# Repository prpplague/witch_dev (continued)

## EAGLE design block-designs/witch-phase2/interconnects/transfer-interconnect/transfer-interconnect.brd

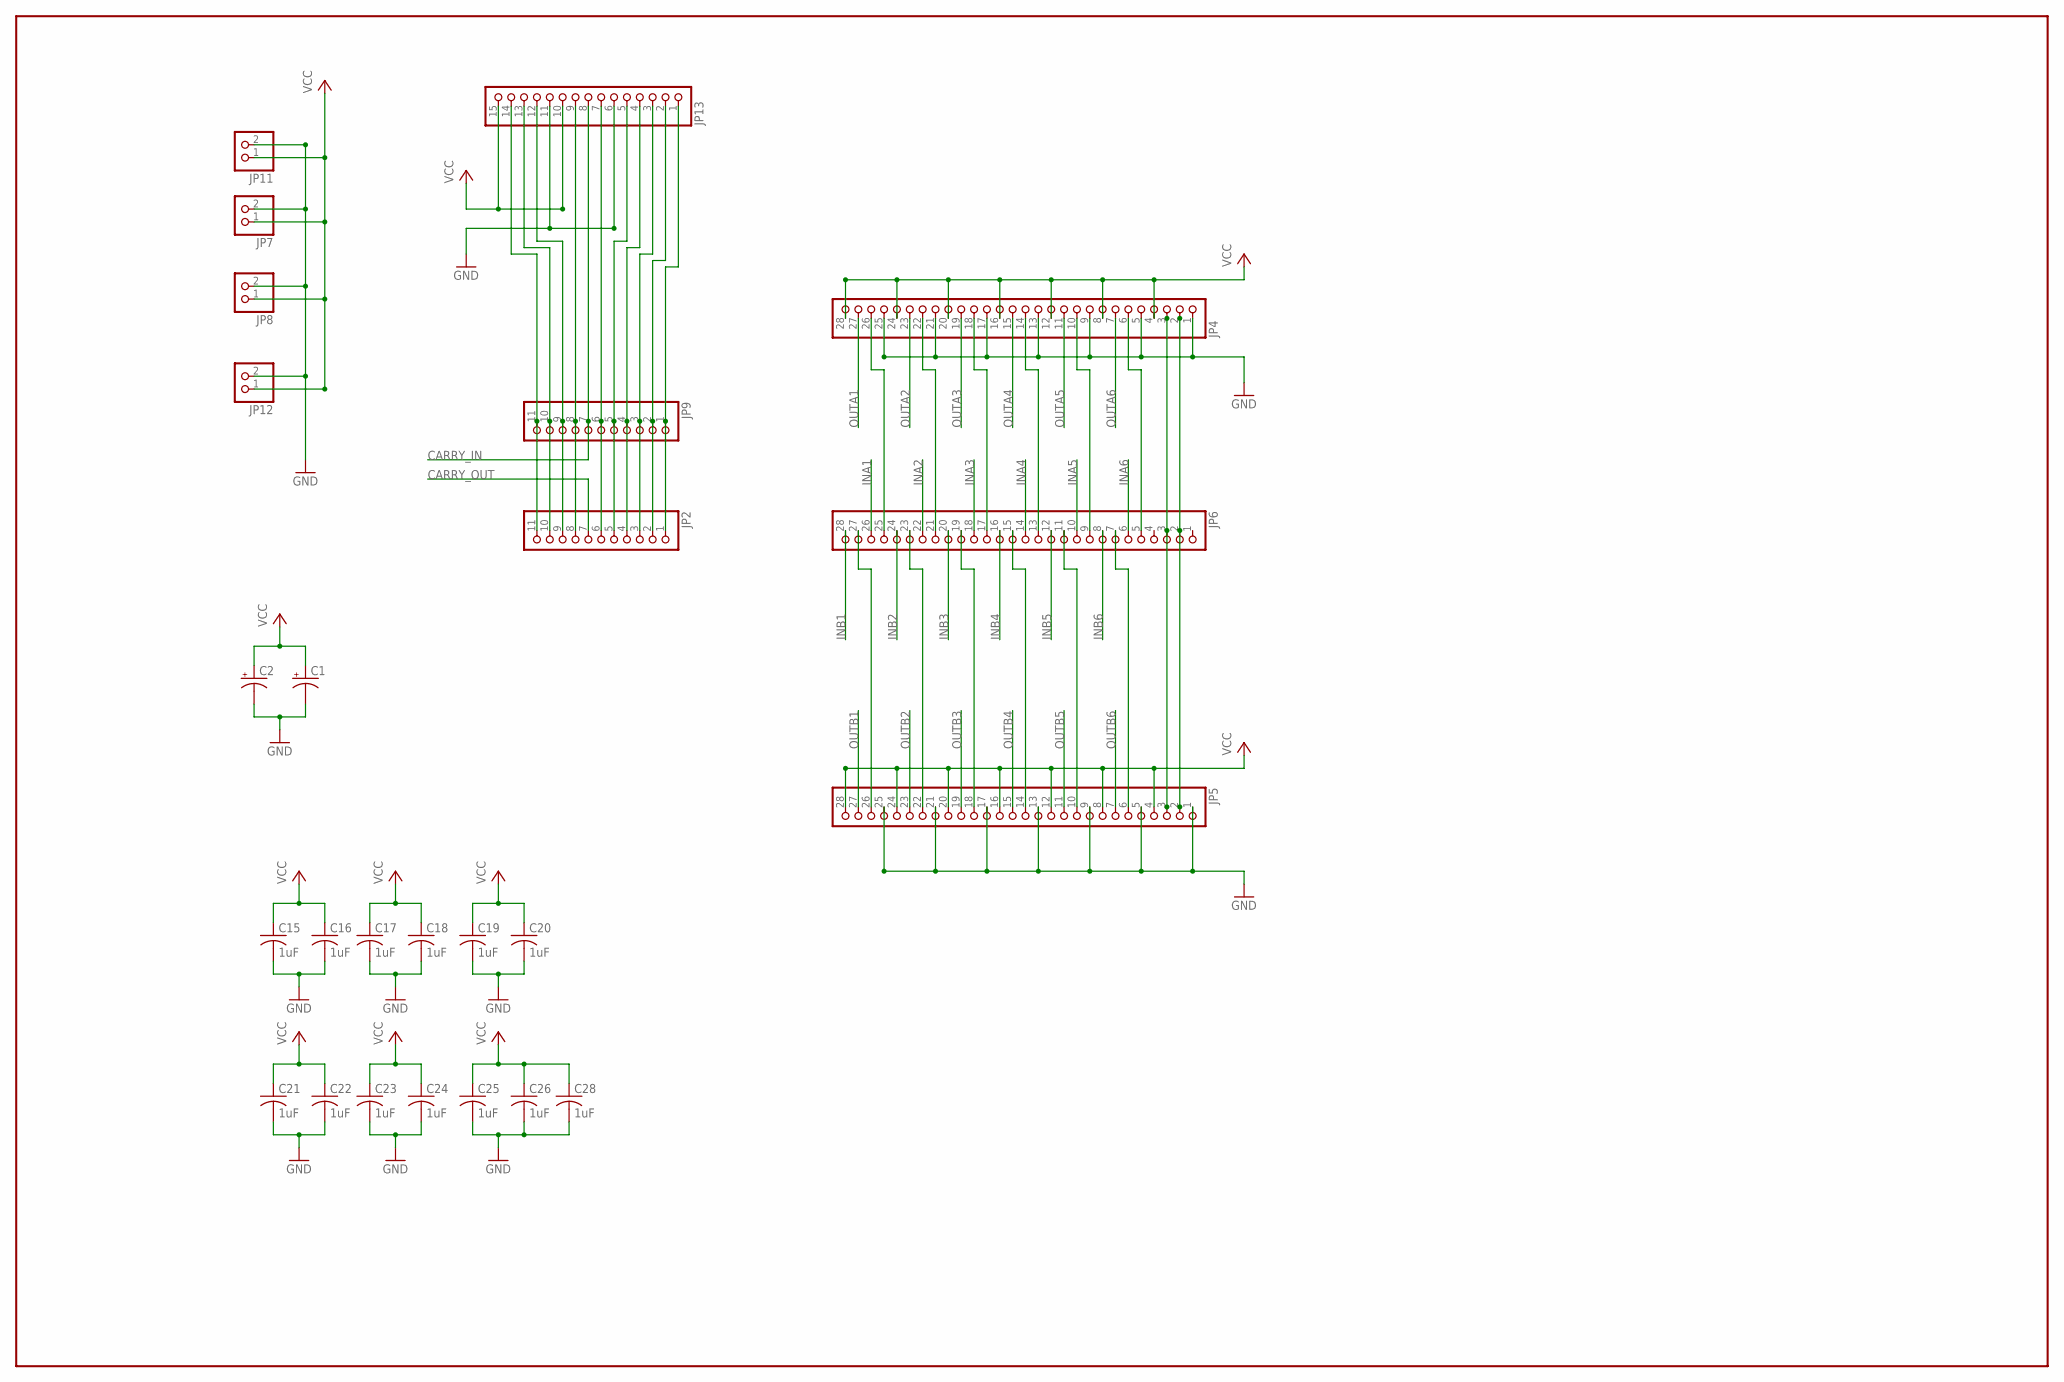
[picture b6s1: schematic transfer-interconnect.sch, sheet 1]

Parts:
C1, C2: CPOL-USE15-6AXIAL; E15-6
C15, C16, C17, C18, C19, C20, C21, C22, C23, C24, C25, C26, C28: 1uF; C0603K
JP2, JP9: PINHD-1X11; 1X11
JP4, JP5, JP6: PINHD-1X28; 1X28
JP7, JP8, JP11, JP12: PINHD-1X2; 1X02
JP13: PINHD-1X15; 1X15

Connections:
CARRY_IN: JP9.7, JP13.8; also elsewhere on the board
CARRY_OUT: JP2.7; also elsewhere on the board
GND: C1.-, C2.-, C15.2, C16.2, C17.2, C18.2, C19.2, C20.2, C21.2, C22.2, C23.2, C24.2, C25.2, C26.2, C28.2, JP4.1, JP4.5, JP4.9, JP4.13, JP4.17, JP4.21, JP4.25, JP5.1, JP5.5, JP5.9, JP5.13, JP5.17, JP5.21, JP5.25, JP7.2, JP8.2, JP11.2, JP12.2, JP13.6, JP13.11; also elsewhere on the board
INA1: JP6.26; also elsewhere on the board
INA2: JP6.22; also elsewhere on the board
INA3: JP6.18; also elsewhere on the board
INA4: JP6.14; also elsewhere on the board
INA5: JP6.10; also elsewhere on the board
INA6: JP6.6; also elsewhere on the board
INB1: JP6.28; also elsewhere on the board
INB2: JP6.24; also elsewhere on the board
INB3: JP6.20; also elsewhere on the board
INB4: JP6.16; also elsewhere on the board
INB5: JP6.12; also elsewhere on the board
INB6: JP6.8; also elsewhere on the board
unnamed: JP4.3, JP5.3, JP6.3
unnamed: JP4.2, JP5.2, JP6.2
unnamed: JP4.10, JP6.9
unnamed: JP2.8, JP9.8, JP13.9
unnamed: JP4.6, JP6.5
unnamed: JP4.14, JP6.13
unnamed: JP2.6, JP9.6, JP13.7
unnamed: JP4.18, JP6.17
unnamed: JP4.22, JP6.21
unnamed: JP4.26, JP6.25
unnamed: JP5.6, JP6.7
unnamed: JP5.10, JP6.11
unnamed: JP5.14, JP6.15
unnamed: JP5.18, JP6.19
unnamed: JP5.22, JP6.23
unnamed: JP5.26, JP6.27
unnamed: JP2.11, JP9.11, JP13.14
unnamed: JP2.10, JP9.10, JP13.13
unnamed: JP2.9, JP9.9, JP13.12
unnamed: JP2.5, JP9.5, JP13.5
unnamed: JP2.4, JP9.4, JP13.4
unnamed: JP2.3, JP9.3, JP13.3
unnamed: JP2.2, JP9.2, JP13.2
unnamed: JP2.1, JP9.1, JP13.1
OUTA1: JP4.27; also elsewhere on the board
OUTA2: JP4.23; also elsewhere on the board
OUTA3: JP4.19; also elsewhere on the board
OUTA4: JP4.15; also elsewhere on the board
OUTA5: JP4.11; also elsewhere on the board
OUTA6: JP4.7; also elsewhere on the board
OUTB1: JP5.27; also elsewhere on the board
OUTB2: JP5.23; also elsewhere on the board
OUTB3: JP5.19; also elsewhere on the board
OUTB4: JP5.15; also elsewhere on the board
OUTB5: JP5.11; also elsewhere on the board
OUTB6: JP5.7; also elsewhere on the board
VCC: C1.+, C2.+, C15.1, C16.1, C17.1, C18.1, C19.1, C20.1, C21.1, C22.1, C23.1, C24.1, C25.1, C26.1, C28.1, JP4.4, JP4.8, JP4.12, JP4.16, JP4.20, JP4.24, JP4.28, JP5.4, JP5.8, JP5.12, JP5.16, JP5.20, JP5.24, JP5.28, JP7.1, JP8.1, JP11.1, JP12.1, JP13.10, JP13.15; also elsewhere on the board

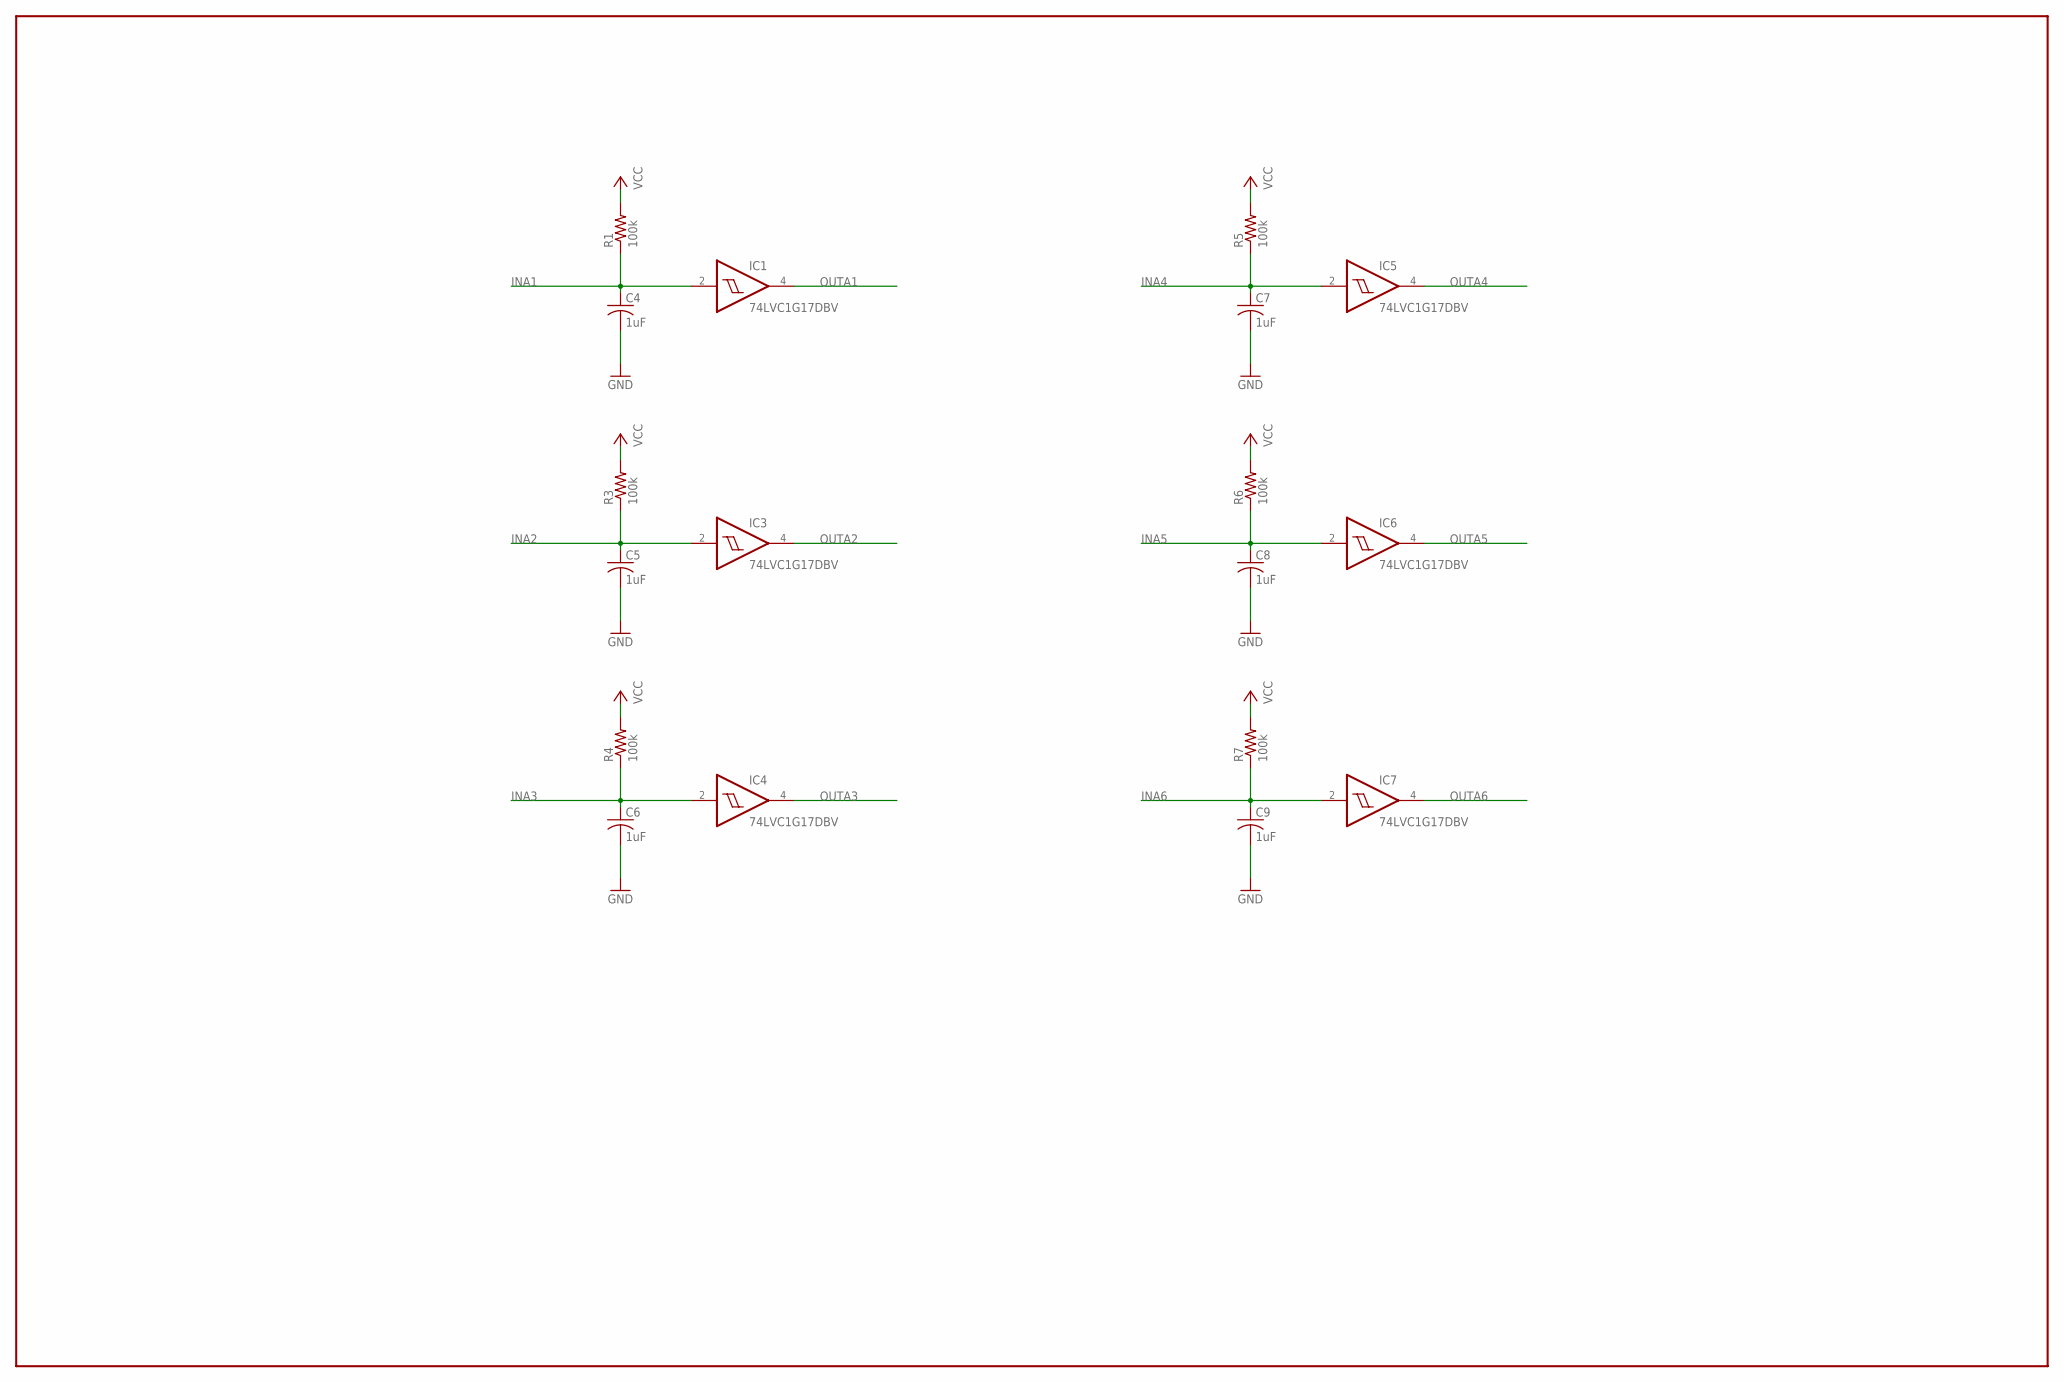
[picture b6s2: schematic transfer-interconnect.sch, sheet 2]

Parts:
C4, C5, C6, C7, C8, C9: 1uF; C0603K
IC1, IC3, IC4, IC5, IC6, IC7: 74LVC1G17DBV; SOT23-5
R1, R3, R4, R5, R6, R7: 100k; R0603

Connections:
GND: C4.2, C5.2, C6.2, C7.2, C8.2, C9.2, IC1.3 (GND), IC3.3 (GND), IC4.3 (GND), IC5.3 (GND), IC6.3 (GND), IC7.3 (GND); also elsewhere on the board
INA1: C4.1, IC1.2 (I), R1.1; also elsewhere on the board
INA2: C5.1, IC3.2 (I), R3.1; also elsewhere on the board
INA3: C6.1, IC4.2 (I), R4.1; also elsewhere on the board
INA4: C7.1, IC5.2 (I), R5.1; also elsewhere on the board
INA5: C8.1, IC6.2 (I), R6.1; also elsewhere on the board
INA6: C9.1, IC7.2 (I), R7.1; also elsewhere on the board
OUTA1: IC1.4 (O); also elsewhere on the board
OUTA2: IC3.4 (O); also elsewhere on the board
OUTA3: IC4.4 (O); also elsewhere on the board
OUTA4: IC5.4 (O); also elsewhere on the board
OUTA5: IC6.4 (O); also elsewhere on the board
OUTA6: IC7.4 (O); also elsewhere on the board
VCC: IC1.5 (VCC), IC3.5 (VCC), IC4.5 (VCC), IC5.5 (VCC), IC6.5 (VCC), IC7.5 (VCC), R1.2, R3.2, R4.2, R5.2, R6.2, R7.2; also elsewhere on the board

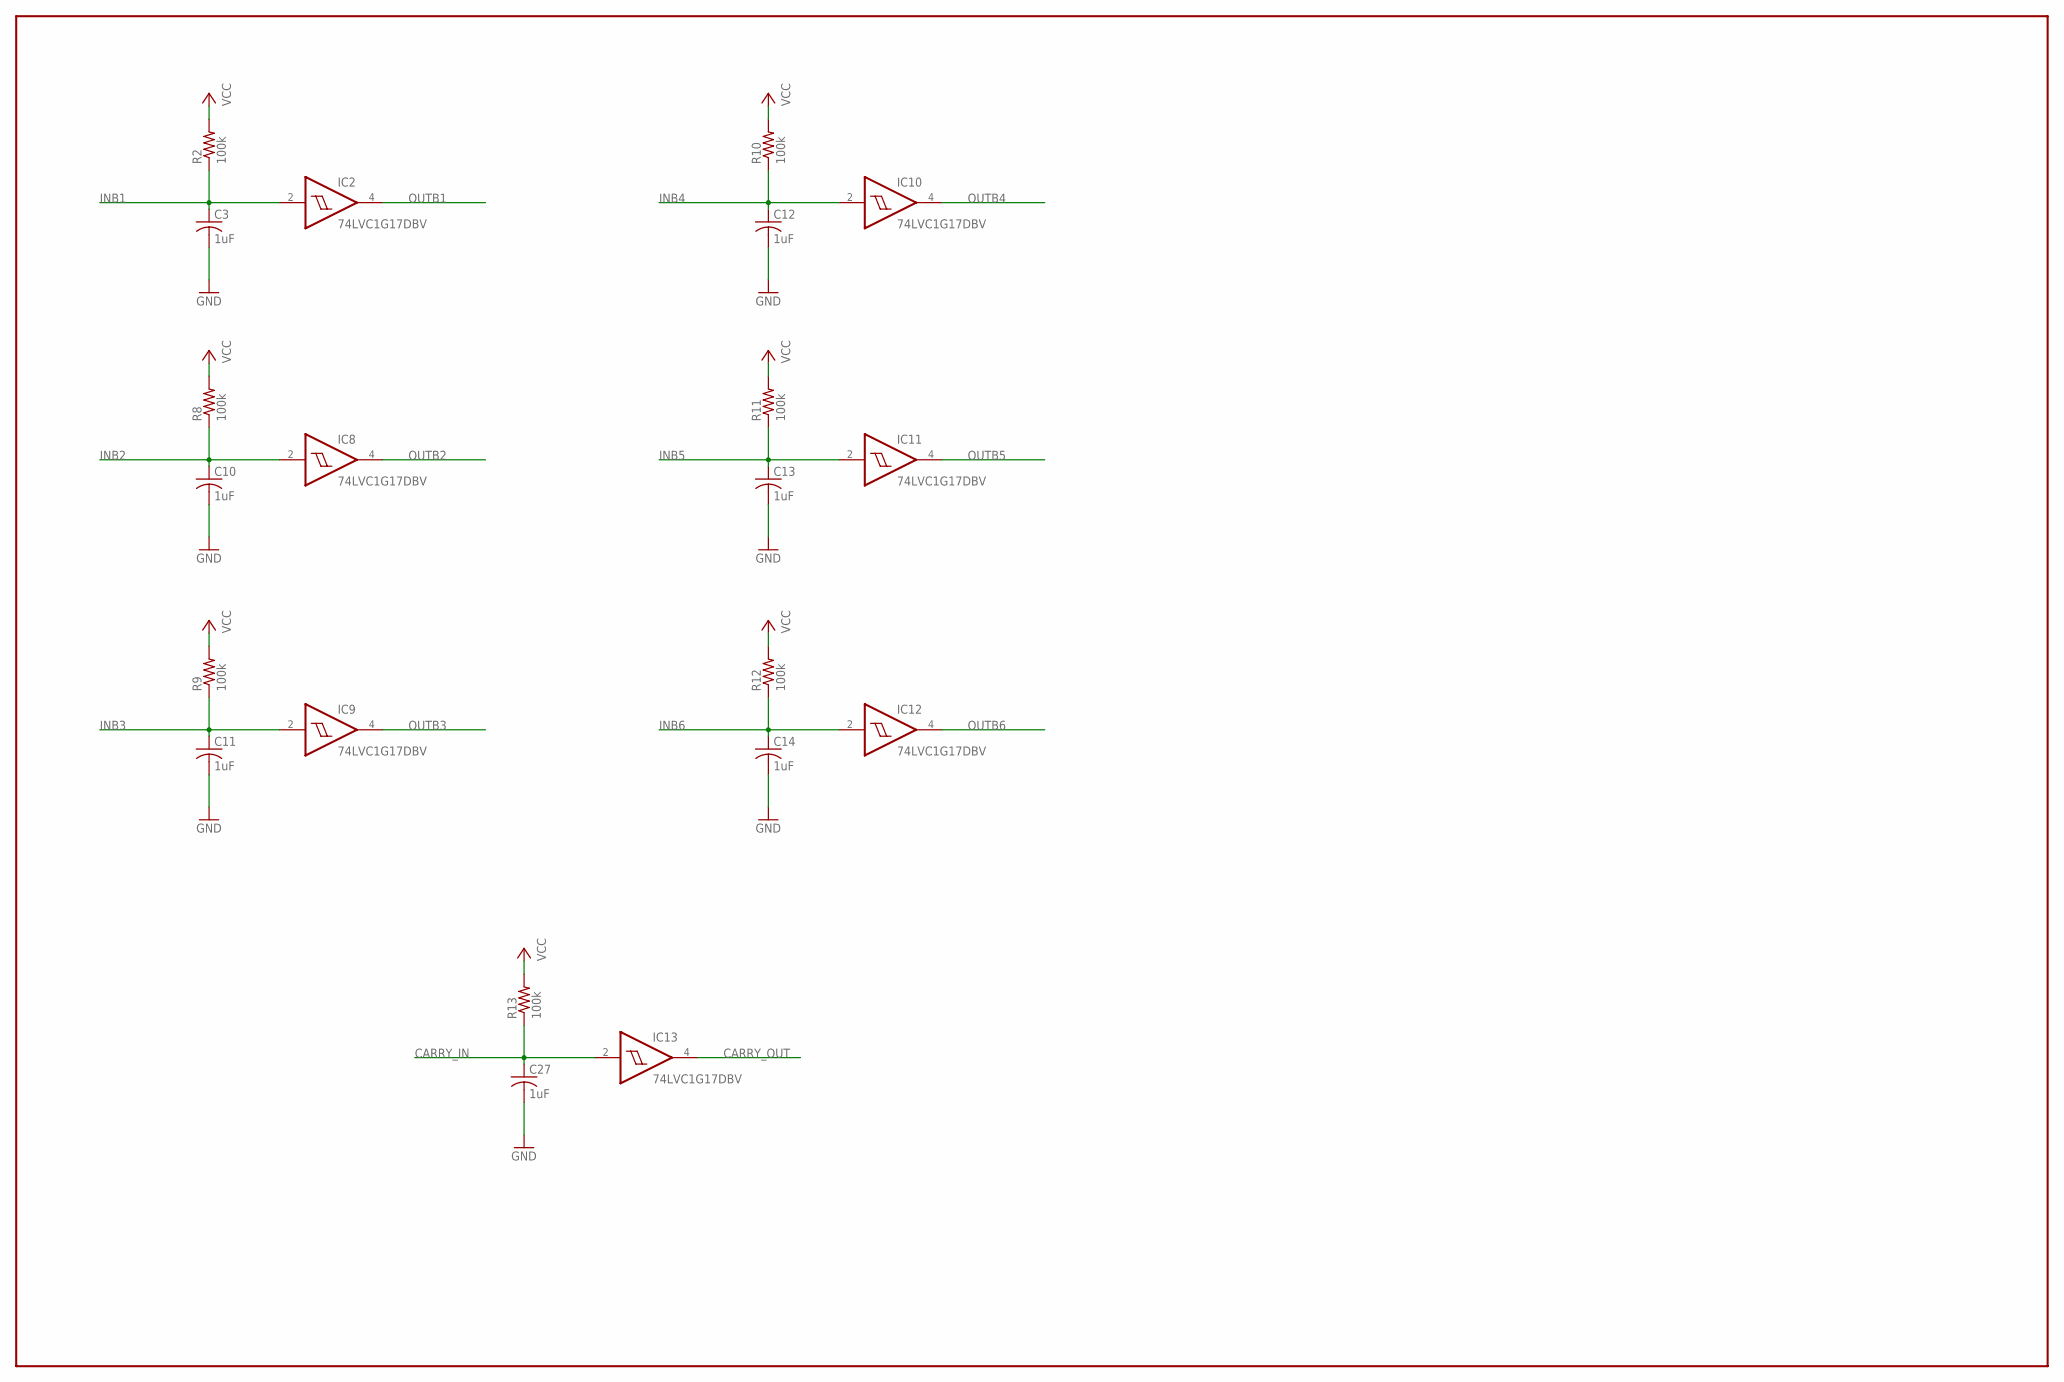
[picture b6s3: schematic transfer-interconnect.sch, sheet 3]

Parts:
C3, C10, C11, C12, C13, C14, C27: 1uF; C0603K
IC2, IC8, IC9, IC10, IC11, IC12, IC13: 74LVC1G17DBV; SOT23-5
R2, R8, R9, R10, R11, R12, R13: 100k; R0603

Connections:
CARRY_IN: C27.1, IC13.2 (I), R13.1; also elsewhere on the board
CARRY_OUT: IC13.4 (O); also elsewhere on the board
GND: C3.2, C10.2, C11.2, C12.2, C13.2, C14.2, C27.2, IC2.3 (GND), IC8.3 (GND), IC9.3 (GND), IC10.3 (GND), IC11.3 (GND), IC12.3 (GND), IC13.3 (GND); also elsewhere on the board
INB1: C3.1, IC2.2 (I), R2.1; also elsewhere on the board
INB2: C10.1, IC8.2 (I), R8.1; also elsewhere on the board
INB3: C11.1, IC9.2 (I), R9.1; also elsewhere on the board
INB4: C12.1, IC10.2 (I), R10.1; also elsewhere on the board
INB5: C13.1, IC11.2 (I), R11.1; also elsewhere on the board
INB6: C14.1, IC12.2 (I), R12.1; also elsewhere on the board
OUTB1: IC2.4 (O); also elsewhere on the board
OUTB2: IC8.4 (O); also elsewhere on the board
OUTB3: IC9.4 (O); also elsewhere on the board
OUTB4: IC10.4 (O); also elsewhere on the board
OUTB5: IC11.4 (O); also elsewhere on the board
OUTB6: IC12.4 (O); also elsewhere on the board
VCC: IC2.5 (VCC), IC8.5 (VCC), IC9.5 (VCC), IC10.5 (VCC), IC11.5 (VCC), IC12.5 (VCC), IC13.5 (VCC), R2.2, R8.2, R9.2, R10.2, R11.2, R12.2, R13.2; also elsewhere on the board

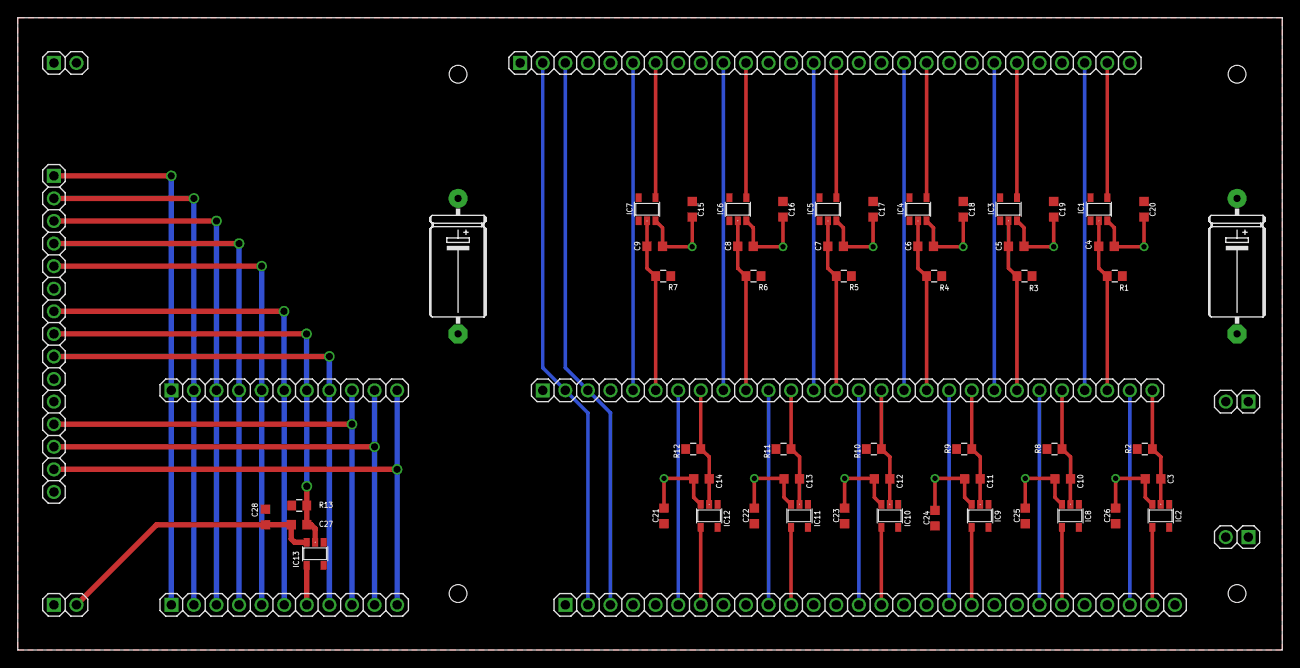
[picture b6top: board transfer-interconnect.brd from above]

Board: 2 copper layers, 142.2 x 71.1 mm, 64 parts (0 on the bottom side), 52 nets.
